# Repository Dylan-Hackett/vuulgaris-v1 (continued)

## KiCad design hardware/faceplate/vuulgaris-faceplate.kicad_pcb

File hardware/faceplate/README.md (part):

# Faceplate PCB

4-layer, **ENIG**. Carries the four capacitive scrub pads on L1 and the MSP430FR2675 on
the back. **The front is exposed gold on ground, and every printed mark is black soldermask**
([ADR 0013](../../docs/decisions/0013-gold-face-mask-ink.md)): order black mask, white silk,
ENIG, via covering "Plugged" (JLC's default; they do not offer tented on 4 layers, and POFV
would cap the pads' vias). 5 boards $79.80 on JLC's instant quote, 2026-09-29. Panel geometry comes from `../../mockups/generate-faceplate.py` — see the
handoff below for the size, which is not what older docs say.

## Status — 2026-09-29: placed, routed, gold face (ADR 0013); DRC clean

**Schematic done**, `mksch → netcheck` 145/145 over 41 nets, every block traced to a TI or
manufacturer figure in `design/design.py`. 54 parts: `U1` MSP430FR2675TPT; `C1`/`C2`
10µF + 100nF on DVCC, `C3` 1µF on VREG, `R1`/`C4` 47k + 1nF on RST (SLASEO5D Figures
10-1, 10-4); `R2`/`R3` 47k on P1.4/P1.5 (SLAU550 §3.3.2.1); `Y1` FC-135 + `C5`/`C6` 22pF
(Figure 10-2); the sixteen CapTIvate lines, **one pin from each block per pad**, each
through a TPD1E10B06 to GND on the electrode side and a 470R series resistor (`D11`–`D44`,
`R11`–`R44`, CapTIvate design guide); `E1`–`E4` the pads as symbols (RX0 on pins 1 and 5,
one net); `TP1`–`TP6` SBW and UART pads; `J1`.

**Pad copper is on the board** (2026-09-28): `E1`–`E4` are generated footprints, one via
per bar (763 vias, 37 bridges), from `design/mkpads.py`; ADR 0003, "Connecting the bars".
boardcheck parity is 0 over 145. **Placed and routed** — every piece of copper from a script,
rebuildable from zero ("Layout" below); DRC 0 errors, nothing unconnected; nothing on the top
layer but the pads, nothing under a pad but its own nets.

**`J1` is the hanxia HX JN2.54-2x5P TP H8.9, LCSC C41376028** (chosen 2026-09-28).
It has to be SMD: `J12`'s through-hole C5665 here would put ten pins through the **front
face**, in the 8mm gap between pads 3 and 4. It is Extended: JLC's Basic filter returns no
SMD 2x5 box header at all. Footprint `IDC-SMD_10P-P2.54_C41376028` is from hanxia's
drawing (`datasheets/hanxia-HX-JN2.54-2x5P-TP-H8.9.pdf`): pads 1.02 x 4.65 on 2.54mm,
11.50 overall; body 20.30 x 8.90, **9.60mm seated**, under the 10mm gap. The runner-up,
XFCN BH254VS-10P (C492446), is 10.5mm tall. The drawing marks pin 1 only by a triangle
on the key wall, so the footprint puts pin 1 on the key-side row at that end, as KiCad's
DIN 41651 footprint and `J12` both do. **Pin 1 and the key are settled from both
manufacturer drawings** (2026-09-28, §5).

## The loop

Same tools as the main board, with `--project faceplate` (`../kicad/tools/proj.py`).
From `hardware/kicad/`, with `set -o pipefail` whenever output is piped:

```bash
python3 tools/mksch.py --project faceplate && python3 tools/netcheck.py --project faceplate
python3 tools/boardcheck.py --project faceplate   # board pads vs netmap parity
python3 tools/drc.py --project faceplate          # KiCad's own DRC -- the clearance authority
python3 tools/drc.py --project faceplate --unrouted   # while placed but not routed: the ratsnest is not a failure
python3 tools/panelcheck.py --project faceplate   # outline, holes, OLED window, J1, the cable, pad copper, vias, walls
```

**Pad copper** is regenerated, never hand-edited: change `mockups/generate-faceplate.py`
(its `--check` must pass), then, under KiCad's Python,
`hardware/faceplate/design/mkpads.py` rewrites the four `SCRUB_PAD_216x10_Pn` footprints
and replaces `E1`–`E4` and every via on a `PADp_RXn` net. panelcheck fails if the board's
pads or vias differ from `copper()` by more than 1µm, or if the generator's via keepouts are
not exactly `J1`'s pad rows.

- **Intent** is `design/netmap.json`; **symbols, sheet positions, footprints** are
  `design/design.py`; values `design/values.json`. Never hand-edit the `.kicad_sch`.
  `J1`'s netmap was derived from the main board's `J12`, pin for pin — the ribbon is
  straight through — and `panelcheck` fails if the two ever disagree.
- **`panelcheck`** is this board's `place.py --check`. It derives everything from the
  generator, the placement file, and the main board itself (its `J12` and the Edge.Cuts
  cutout). Parts not placed or not yet sized are **TODO**, not failures; run it with
  `--strict` before plotting a fab package and every TODO fails.
- **Pin cache:** `design/kpins.json` is untracked. Rebuild it, from the repo root, with
  exactly this argument list (stock libraries first, the shared project library last):

  ```bash
  python3 hardware/kicad/tools/ksym.py --project faceplate /Applications/KiCad/KiCad.app/Contents/SharedSupport/symbols/*.kicad_sym hardware/kicad/lib/vuulgaris.kicad_sym
  ```
- **The board** was bootstrapped once by `design/mkboard.py` (KiCad's Python; it refuses
  to overwrite). From here it is edited like the main board's: scripted through pcbnew,
  or by hand in Pcbnew — and after a script writes, **File → Revert** before touching it.
- **Coordinates:** the faceplate board is drawn in panel coordinates, sheet = panel +
  (100, 50) (`panelgeo.FACE_ORG`). Panel y runs from the jack edge.
- The library is **shared** with the main board (`../kicad/lib/`, via this project's
  `sym-lib-table` / `fp-lib-table`). Footprints named `lib:name` in `design.py` come
  from elsewhere; a bare name means `vuulgaris.pretty`.
- DRC ran with one warning while `J1` was KiCad's stock footprint, which does not
  resolve in headless pcbnew. With the real part in the project library it is 0 and 0.
- Every check has been watched failing: a swapped netmap pin (netcheck, panelcheck), a
  track shorting pins 1 and 3 (DRC, boardcheck), `J1` moved 0.5mm or turned 180°, a pot
  hole 0.5mm undersize or 0.3mm off (panelcheck).

## Handoff from the main board — 2026-09-24

The main board is finished: DRC clean, fab package at `../vuulgaris-v1-fab.zip`. What
follows is fixed by it. The faceplate works around these, not the other way round.

### 1. Size: the generator is the source of truth — DONE 2026-09-27, 298.286 x 137.81mm

`generate-faceplate.py` gives **298.286 x 137.81mm**: the 130.81mm composition frame
(`composition_h_mm`, "board + 14" as of 2026-08-26) plus `panel_top_extra_mm` 2.0 and
`panel_bottom_extra_mm` 5.0, both pure extensions. `--check` re-derives with the extras
zeroed and fails if any placement row moves other than y += 2, and asserts the cavity is
1 + 118.81 + 6. Numbers still in circulation that are **superseded**: 130.81, "~285 x 155",
"298 x 154" (`panel-budget.md`). The mockup SVGs are now `mockups/faceplate-v1.svg` and
`faceplate-v1-FAB.svg`; they were `-298x139`, which was never their size.

- **+2mm at the top (jack) edge — DONE 2026-09-27.** Every one of the 24 rows in
  `../placement-panel-facing.txt` moved +2.000 in y and nothing else (compared in integer
  thousandths), `OY` went 7.000 → 9.000 in the same commit, and `place.py --check` reports
  all 24 on their holes with output identical to before; with the old `OY` it reports all
  24 off by 2.0. What the requirement was: The main board's top edge moved out 2mm on
  2026-09-23 so every edge connector ends flush with the wall (`design-state.md`, "Top
  edge extended 2mm"); the board is now 118.81mm. The knobs did not move, so **every
  panel y grows by exactly 2.000 and nothing may re-flow.** The generator centres and
  scales parts of the composition, so do not just raise `panel_h_mm`: add a pure offset,
  regenerate `../placement-panel-facing.txt`, and diff it against the old one — every
  row +2.000 in y, nothing else. In the **same commit** set `OY` in
  `../kicad/tools/place.py` from 7.000 to 9.000 (the comment above `ORG` explains), and
  `place.py --check` must still report all 24 panel parts on their holes. Get this wrong
  and `place.py` moves 24 parts on a routed board.
- **+5mm more at the bottom (back) edge — DECIDED 2026-09-27: yes, 137.81mm.** "Board +
  14" leaves 1mm behind the board, but the board slides in along y and needs 6mm of
  travel to clear the jacks (`design-state.md`, "Assembly": cavity 125.81 = 1 + 118.81 +
  6), so the box is 137.81 outside. A 132.81 panel on that box stops 5mm short of the
  back wall's outer face: its back screws (3mm in) would land over the cavity, and pad 4
  would end 0.36mm from the wall's inner face. The 5mm goes on below pad 4 and **moves no
  coordinates**. The cost is look: the pad block now sits 6.36mm below the divider and
  11.36mm above the bottom edge. Re-centring it would move ENC0 and SW4–SW9, which are
  centred on the pad block, so it stays.

Pads — **RECONCILED 2026-09-27: the generator's geometry, 10mm wide, 8mm gap, 18mm
pitch, 100 teeth.** See "Pad geometry" below and ADR 0003. Both candidates sat on the
same 18mm pitch, so the pad centres (and ENC0, centred on them) come out identical
either way; this was a sensing decision, not a placement one.

### 2. Stack-up: the pots are the datum, and the faceplate is structural

- Faceplate underside **10.0mm** above the main board (the pots' mounting surface),
  **1.6mm** thick, outer face at 11.6mm.
- **Do not go thicker.** The pots (Alpha RD902F) have 3.4mm of M7x0.75 thread above the
  outer face, for a 1.8mm nut plus washer.
- The six pot nuts are the **only** clamp. Encoders (EC12, 0.9mm of bushing through),
  toggles, buttons and the OLED locate but carry nothing. The whole main board hangs off
  the faceplate through those six nuts (`design-state.md`, "Panel mounting").
- **The 10mm gap is shared.** Anything on the faceplate's back (the MSP430, the ESD network,
  LEDs, the connector) sits in the same 10mm as the main board's top-side parts beneath it.
  The tall ones, board coordinates (panel = board + (6.995, 9.000) once §1's offset is in):

  | main-board part | height | board bbox x0,y0 – x1,y1 | faceplate room above |
  |---|---|---|---|
  | `C36`, `C37` electrolytics | 7.8mm | 190–200, 72.8–90.9 | ~2.2mm |
  | `C32`, `C33` electrolytics | 5.4mm | 190–201, 50.1–68.3 | ~4.6mm |
  | `U1` Daisy Patch SM | ~7mm soldered direct (no 3D model) | 243.8–283.9, 47.2–115.4 | ~3mm |
  | `VT301`/`302`/`401`/`402` vactrols | unknown (no 3D model) | 132.6–165.3, 58.0–67.8 and 134.9–167.5, 91.1–100.9 | read the Xvive drawing |

  Everything else on the main board's top is under 3.5mm apart from the panel parts, which
  pass through. Keep faceplate back-side parts low over those areas, or put them elsewhere.
  **The Daisy must be soldered in or on low-profile sockets** — standard 8.5mm sockets put
  it near 13mm and into the faceplate.

### 3. Holes

| part | hole | source |
|---|---|---|
| pots `RV1`–`RV6` | **7.5mm**, centred **0.17mm toward the top edge** of the panel coordinate | M7x0.75, washer ID 7.2 (Alpha drawing); true shaft is (0, −5.00) from the footprint origin, placed at −4.83 — `place.py` |
| buttons `SW4`–`SW9` | **7.2mm** | TS1103S drawing: plunger 6.2 ±0.2 at 14mm height; 0.4 a side at the largest, over the faceplate's ±0.25 float. Generator `mx_cut_d_mm` (the layout keeps `mx_hole_r_mm` = 3.3: changing that re-flows the column). Was 6.6 — 0.1 a side, a sticky button |
| toggles `SW1`/`SW2` | **5.6mm** | Dailywell drawing: 10-48 UNS bushing, 4.83 over the thread. Its 4.95 hole is for a switch hung from the panel by its nut; ours is soldered to the main board too, so the hole takes the bushing's ±0.25 and the faceplate's float. Generator `switch_hole_d_mm` |
| encoders `ENC1`–`ENC8` (EC12E) | **9.5mm** | ALPS EC12E2430803 drawing: body 5.5, then 7mm of M9x0.75 -- the static thread passes the faceplate; M9 + 0.5, the pots' margin |
| encoder `ENC0` (EC11L) | **10.0mm** | ALPS EC11L1525G01 drawing (LE2115L02G): **no thread** -- a 7mm bushing ends 9.5mm up, then a knurled 9.03mm shaft that turns and pushes 1.5mm passes the faceplate. Running clearance |
| OLED `DS1` | **window, 60.09 × 33.90mm**, r 1.0 corners, panel (208.50, 15.15)–(268.59, 49.05) | §4; the generator's `oled_window()` |

**Corners — filleted 2026-09-28, r 6mm** (generator `panel_corner_r_mm`), the wall
thickness. **The enclosure's outer corners take the same radius**; at 6 the cavity keeps
square inside corners, so the main board's outline is untouched. The cost: a panel screw
can no longer sit in the corner — at 3mm in, its head has to clear the arc, so corner
screws go **at least 9mm along the edge** (`panel_screw_corner_min_mm`, checked).

**Panel screws — 2026-09-28:** four M3, 3.4mm clearance holes, one at each corner: on the
long edges 9mm from the corner (x 9.00 / 289.29) and 3mm in (y 3.00 / 134.81), as close as
the r6 corner lets an M3 pan head sit. (Ten, along the edges, until the same day.) Generator
`panel_screws()`; the enclosure's threaded inserts go under them. The mockup draws the
heads; the board does not print them.
panelcheck checks all four corners.

The generator draws **no pot or encoder holes at all** — the r=8 and r=9.2 circles in the FAB
SVG are knob outlines, not cuts. The board's holes are drawn by `design/mkholes.py` from
`panelgeo.holes()`, and the OLED window from `panelgeo.oled_window()` (2026-09-28).
panelcheck `--strict` has no TODO left.

### 4. OLED

The module is **68 x 43mm on its own PCB, 4.2mm tall**, active area 55.01 x 27.49mm. It will
be raised **3–5mm** on a 1x9 socket plus four M3 standoffs in the corner holes already on
the main board. **Nylon standoffs, not metal:** the lower-left hole (297.55, 94.05) has a
`POS12V` trace on F.Cu 2.2mm from its centre, under the standoff's hex base, and a metal
one would put +12V a scratch of soldermask away from the module's mounting hole. The
other three holes have no copper within 3mm on either side. Its face then sits about **2.4–4.4mm** behind the
outer surface; at 5.8mm of lift it hits the faceplate. This answers Q18.

**The window — sized 2026-09-28** by the generator's `oled_window()`, from the HS242L01
drawing (datasheets/, section 1.4: PCB **72** × 43 — the spec table's "68 × 43" is the hole
pitch; AA 55.01 × 27.49 centred along the long axis, **5.11mm below the top edge and 10.4mm
above the bottom**; glass 62.1 × 39.85) and the stack-up. The lift is not chosen, so it is
sized at the **deepest**, 3mm: face 4.4mm below the outer surface.

| | |
|---|---|
| active area, panel | x 211.04–266.05, y 17.16–44.65 |
| window | x 208.50–268.59, y 15.15–49.05 (60.09 × 33.90), r 1.0 |
| AA in view, at 4.4mm deep | 45° from the player's side, 30° from the sides, 25° from the back |
| never nearer the glass edge than | 1.0mm, so past the pixels you see black glass, not the module PCB |

It is lopsided on purpose: the wide black band on the glass, where the flex bonds, is on
the player's side, which is the side that needs the margin. panelcheck checks the drawn
window against the generator, and the generator's module centre against the main board's
four `DS1` holes. **No chamfer:** JLC cannot bevel an internal cutout in FR4; the walls are
straight 1.6mm, and a hand bevel is optional.

### 5. The connector

Main board `J12`: 2x5 2.54mm box header (LCSC C5665), **on the BACK of the main board,
facing down** (moved 2026-09-25), ribbon to the faceplate.

**The route.** The main board has a **24 x 12mm cutout** directly beside `J12`, at board
(210, 97.5)–(234, 109.5) — sheet (310, 147.5)–(334, 159.5) — made for exactly this. The
faceplate's connector sits **over that cutout, facing down**; its ribbon plug hangs through
the hole in the main board, and the ribbon runs underneath to `J12`. That is what makes the
10mm faceplate gap workable: neither mated plug has to fit inside it. So:

- **Put the faceplate header over the cutout, centred on board (222.0, 103.5)** — panel
  (228.995, 112.5) once §1's offset is in. A 2x5 IDC plug is about 20.3 x 9mm; the hole is
  24 x 12, so 1.5–2mm clear per side. Checked 2026-09-26: `J12` is centred on the cutout
  in x (0.00mm), its body 1.44mm from the cutout's edge, nothing sits in the cutout, and
  nothing else is on the main board's back in the ribbon's path.
- **`J12`'s pin 1 is at its +x end (right, viewed from the top), on the row nearest the
  cutout.** Orient the faceplate header so the ribbon takes pin 1 to pin 1 — the two plugs
  sit at different depths, so it is easy to get backwards on paper. Done below.

  **Paper mock-up, 2026-09-28** (both boards read through pcbnew, panel coordinates):

  | | centre | pin 1 | odd row | key (slot) | faces |
  |---|---|---|---|---|---|
  | main `J12` (C5665) | (228.995, 100.5) | +x end | +y | +y wall (footprint silk) | down, from the main board's back |
  | faceplate `J1` (hanxia) | (228.995, 112.5) | +x end | +y | +y wall (hanxia drawing) | down, from the faceplate's back |

  The two headers are the **same orientation**, 12mm apart in y and at different heights;
  the cutout is on `J12`'s +y side, `U7` on its −y side (y 82). So the cable is a plain
  straight 10-way IDC ribbon, both sockets pressed on the **same face**, red stripe at the
  triangle on both. It leaves `J12`'s socket toward +y (the cutout, away from `U7`), sags
  under the main board, and rises into `J1`'s socket from its −y side: no fold, no twist.
  Pin mapping then does not depend on the sockets at all -- each is keyed into an
  identically oriented header, so wire n lands on pin n at both ends, whatever the socket's
  own convention.

  That argument needs both headers to carry the key on the same side of pin 1 -- were
  C5665's on the other wall, a keyed socket would sit 180° round at `J12` and the cable would
  map pin n to 11−n, `P3V3_MSP430` onto `GND`. **Closed from both manufacturer drawings,
  2026-09-28:** hanxia's (`datasheets/hanxia-HX-JN2.54-2x5P-TP-H8.9.pdf`) and BOOMELE's for
  C5665 (`datasheets/BOOMELE-C5665-2x5-box-header.pdf`, from JLC's part page -- LCSC's link
  is dead) both mould the pin-1 triangle on the **keyed wall**, at one end. So the key is on
  the pin-1 row on both parts, which is what both footprints assume (`J12`'s silkscreen,
  `J1`'s Fab notch). C5665's drawing also confirms `J12`'s 1.0mm holes on the 2.54 grid.
  What is left is assembly, not design: use a straight cable, both sockets on the same face,
  red stripe to the triangle. Plugging in the first real cable is still a free sanity check.
- **`U7` (the DKM10, ~10mm tall, on the back) is 1.03mm from `J12`'s far side.** A plug
  sits inside the header's shroud, so it fits; run the ribbon out toward the cutout, not
  toward `U7`.
- **Leave the ribbon slack.** The faceplate end is plugged in with the faceplate lifted and
  then lowered onto the pots, so the cable folds under the main board rather than spanning
  the 12mm between the plugs taut.
- **The case floor needs about 15mm below the main board** around `J12` and the cutout: a
  9.2mm header plus the mated plug and the ribbon's fold.

| pin | net | |
|---|---|---|
| 1 | `MSP_TEST` | |
| 3 | `MSP_RST` | driven by MCP23017 `U4` |
| 5 | `MSP430_RXD` | Daisy A3 (UART4 TX) → MSP430 |
| 7 | `MSP430_TXD` | MSP430 **drives** → Daisy A2 (UART4 RX) |
| 9 | `P3V3_MSP430` | its own AMS1117 (`U6`) on the main board |
| 2,4,6,8,10 | GND | |

The order runs backwards from the original (pin 1 was 3V3) because flipping the header to
the back mirrors it; every net kept its hole and its routing. **Pin 1 is the ribbon's red
stripe** — check it end to end with the faceplate header's orientation before ordering
that board.

**No I2C and no IRQ cross the cable** (`pin-allocation.md`, superseding design-state §9).
There is **no 5V** on it, by decision (ADR 0012).

### 6. MSP430

- UART on UCA0 at its **default** pins (P1.4 TXD / P1.5 RXD, pins 4/5), per
  `pin-allocation.md`. UART and I2C do not share pins (Q2, resolved).
- **Q21 CLOSED 2026-09-27.** SLAU550 §3.1 defers the BSL pins to the device datasheet;
  SLASEO5D Table 9-4 gives the UART BSL as **P1.4 transmit / P1.5 receive**, PT pins 4/5
  (Figure 7-1). The runtime UART and the BSL are the same two wires. The remapped
  P5.1/P5.2 (44/45) fallback is **dropped**: it only ever covered the BSL being elsewhere,
  and `J12` has no free position to carry it.
- **47k pull-ups on P1.4 and P1.5.** They are also TCK/TMS, and SLAU550 §3.3.2.1 warns that
  floating TCK/TMS raise the odds of landing in JTAG mode; the pull-ups also stop RXD
  floating while the Daisy boots. SLAU550's 1nF pull-downs are left off: they target the
  hardware entry sequence, which production never uses (blank-device detection, then
  software invocation).
- Q22: plan the crystal. SBW pads (TEST, RST, 3V3, GND) and test points on TX/RX/RST/TEST.

### 7. LEDs — DECIDED 2026-09-27: none. See ADR 0012.

No LEDs on this faceplate, and no 5V on `J12`. The main board orders as it is. What was on
the table (2026-09-23): one LED per zone, 16 in all, red/amber on 3.3V or white/RGB on a
new 5V pin, driven from the MSP430 through shift registers, lit beside the zones through
small windows and never PWM'd during a touch scan.

## Contents

```
vuulgaris-faceplate.kicad_pro / .kicad_sch / .kicad_pcb
sym-lib-table, fp-lib-table   point at ../kicad/lib, shared with the main board
design/netmap.json            the intent
design/design.py              symbols, sheet positions, footprints (read by mksch.py)
design/values.json            Value fields
design/mkboard.py             the one-shot board bootstrap
design/mkpads.py              pad footprints + E1-E4 + their vias, from the generator's copper()
design/mkplace.py             the one-shot placement of everything else (the table above)
design/mkholes.py             the whole Edge.Cuts layer: outline (r 6 corners), panel holes, screws, OLED window
design/mkbuses.py             the pad buses: every bar's via joined, each net out to the margin (deterministic)
design/mkcells.py             the network grid's cell vias, TVS/R stubs and TVS grounds (deterministic)
design/mkescape.py            J1 out along the pad 3-4 corridor to the test pads, R2, R3 and U1 (deterministic)
design/mkfanin.py             the L2 fan-in: every bus exit to its cell via, crossing-free (deterministic)
design/mkface.py              the front (ADR 0013): the GND gold on F.Cu, the art as black mask, the via patch and dots, the silk
design/mkzones.py             the L3 GND plane: solid, in the margin and the pad 3-4 corridor, never under a pad
design/mkroute.py             everything else, by Freerouting, fenced: no F.Cu, nothing under or between the pads
design/mklib_faceplate.py     the faceplate's own library parts (U1, Y1, the TVS, the pad symbol);
                              the pin table twice (Figure 7-1, Table 7-1), checked equal
DRC.rpt                       from tools/drc.py --project faceplate
fab/                          the fab outputs ("Fab package"); zipped to ../vuulgaris-faceplate-fab.zip
```

The SLAA891 cross-check came back as a connectivity finding, not a geometry one: TI's
elements are single bodies and ours are ratio-encoded islands, so there is no TI pattern to
diff against (ADR 0003, "Connecting the bars").

## Pad geometry

Authoritative spec is [ADR 0003](../../docs/decisions/0003-comb-pad-rx0-wraparound.md).
Summary: 4 channels, 5 segments, 4 zones, order `RX0 RX1 RX2 RX3 RX0`.

**Settled 2026-09-27**, and what `../../mockups/generate-faceplate.py` draws:

| | |
|---|---|
| Pad length | 216mm, independent of the gap (the "12 x pitch" lock was an artefact — Q17) |
| Pad width | **10mm** |
| Gap / pitch | **8mm / 18mm** |
| Teeth | **100** (25 per zone), 2.160mm pitch, 1.950mm wide, 0.21mm apart |
| Top-to-bottom gap | 0.20mm |
| Tooth fillet | 0.6mm, with the bar heights area-compensated so it does not bend the position curve |
| Min copper | 0.15mm enforced; the thinnest bar drawn is 0.197mm |

Why 10/8 rather than the old 12/6: the gap is the untested crosstalk variable (Q17) and
wants to be as wide as the pitch allows; bare copper already gives more signal than TI's
overlay designs, so 12mm buys sensitivity that is not needed at the cost of base
capacitance; and ratio encoding reads a finger that rides high or low across the pad as a
position error (top bars are RX0/RX2, bottom RX1/RX3), which a pad closer to a fingertip's
width keeps smaller. The old "80 teeth at 2.19mm" was the 175mm pad's number; at 216mm, 80
teeth would be 2.70mm.

The copper comes from `generate-faceplate.py`, not `comb-pad-generator.html`, whose
defaults are the superseded 175mm / 12mm pad. Its SVG is true mm scale with one `<g>` per
net.

**Cross-check against TI's own SLAA891 OpenSCAD output before committing copper.**

## Layout — placed and routed 2026-09-28

Settled with Dylan, in order: (a) one open via per bar (ADR 0003, "Connecting the bars");
(b) `U1` and its networks in the **right margin**, not the centre (ADR 0003, layout rules);
(c) the UART, 3V3, RST and TEST from `J1` along the **gap between pads 3 and 4**. Then:
route everything, **nothing on the top layer** (it is the scrub pads and nothing else).

All parts on B.Cu. The margin strip is panel x 277.14 (copper ends) to 292.29 (the wall's
inner face, where the faceplate rests on the wall top — panelcheck fails any back-side part
past it), over the Daisy (~3mm clear; nothing here is over 1.6mm).

| where (panel) | what |
|---|---|
| `U1` (284.45, 104.0) | CAP pins 23–39 face **up**, digital corner (46–5) down-right. Pins 1–5 run right to left along the bottom, 46–48 up the right side |
| the 4 × 4 grid over the CAP pins, rows y 77.15 / 83.15 / 89.15 / 95.15 (6mm apart) | the 16 networks. **Column = CapTIvate block** (RX0–RX3 at x 280.30 / 283.50 / 288.00 / 290.92, each over its own pins: CAP0 = 23–26 … CAP3 = 36–39), **row = pad** (1 at the top). Each cell: its via, the TVS on top of its 470R (pin 1 over pin 1, ground to the right; ADR 0004: the order and a short ground are what count) |
| middle channel, over pin 31 | `C3` 1µF VREG |
| across the corner by pins 1 / 48 | `C2` 100nF |
| right edge, y ~112–116 | `Y1` stood on end, `C5` (XIN) / `C6` (XOUT) beside its two pads |
| above the corridor's mouth, (278.3, 106.2) | `C1` 10µF 3V3 bulk — in the mouth it blocked RST, TXD and RXD in turn |
| under `U1`'s bottom-left | `C4` / `R1` (RST RC), `R3` (RXD pull-up, beside pin 5) |
| the corridor, x 240–262 | `TP1`–`TP6`, each ON its own line, staggered; `R2` (TXD pull-up) across the 3V3 and TXD lines; `TP4` (SBW GND) by `J1`'s GND via |

Pitches come from the silk (R0603's box is 1.47 × 2.93), not the library's small courtyards:
0 silk overlaps. The 31 silk-over-copper warnings are the library's R/C pin-1 dots, clipped
by the mask, as on the main board. The 470Rs' references stand on end beside them; the TVS
and test pad references are on B.Fab.

### How it is routed — rebuildable from zero

Every piece of copper comes from a script, in this order (KiCad's Python, from the repo root):

```bash
KPY=/Applications/KiCad/KiCad.app/Contents/Frameworks/Python.framework/Versions/3.9/bin/python3
$KPY hardware/faceplate/design/mkroute.py --unroute    # every track and via off
$KPY hardware/faceplate/design/mkplace.py --force      # the parts (the table above)
$KPY hardware/faceplate/design/mkholes.py              # Edge.Cuts: outline, holes, screws, OLED window
for s in mkpads mkbuses mkcells mkescape mkfanin mkzones; do $KPY hardware/faceplate/design/$s.py; done
$KPY hardware/faceplate/design/mkroute.py              # the rest, by Freerouting; re-run until DRC is clean
$KPY hardware/faceplate/design/mkface.py               # the front: gold, mask art, silk -- last, it clears the vias
```

**The corridor's right end is Dylan's hand reroute** (2026-09-29), now carried by the scripts.
The TXD and RXD hops and C4's GND via sit under the via patch. `mkescape.py` draws TXD, RXD,
RST and TEST end to end from its `TAIL` table, including the router's old runs past C4,
which the reroute kept, so the router finds those four nets complete. `mkfanin.py` jogs pad
4's RX0 exit to y 117.15.

| script | draws | how |
|---|---|---|
| `mkpads` | the pad copper, one via per bar | the generator's `copper()` |
| `mkbuses` | the buses: every bar's via joined, each net out to the margin | exact, L2 (RX0's join on L3); every via on a segment end |
| `mkcells` | each cell's via and B.Cu down to TVS pin 1 and R pin 1; each TVS's GND via; `C3`'s ground | exact; the vias staggered in height (below) |
| `mkescape` | `J1`'s escape, the corridor, its taps; RXD and TXD's hops to `U1`; `J1`'s GND | exact, B.Cu (hops on L2) |
| `mkfanin` | all 16 electrode lines, bus exit to cell via | exact, L2 |
| `mkzones` | the L3 GND plane: **solid**, margin + corridor, never under a pad | exact |
| `mkroute` | everything else: the B.Cu fan-out into `U1`, power, the last grounds, crystal | Freerouting, fenced (the gold is dropped from its DSN); then prunes dangling copper and stitches any GND pad with no path to the plane |
| `mkface` | the front: one GND zone on F.Cu less each pad's 2mm frame; F.Mask openings = the gold less the mask block (frames + via patch as one filleted outline), a dot over every other via outside the pads, and every art stroke; the right-hand numerals in silk on the patch | the generator's `face()`, `mask_block()`, `scale_marks()`, `panel_art()` (ADR 0013) |

**The electrode fan-in (`mkfanin`).** Each pad's lines leave its bus as RX0, RX2, RX1, RX3
(top to bottom) but the columns run RX0, RX1, RX2, RX3. Each cell's via sits at its own height
in the cell band, 0.5 apart, in the order the lines arrive, so each line runs level to its own
column and passes the others' vias at ≥ 0.5 — never another line. Pads 1–3 come in from the
strip left of the grid (column 0's via steps 0.4 right to open a fourth slot); pad 4's would
jam it, so they run under the corner group, up a strip at the right edge, and in from the
right, its via order reversed.

**The corridor (`mkescape`).** `J1`'s inner four signals climb into the 2.2mm channel between
its rows in pin order; past `J1` all five fan out to 1.3mm (RXD straight, the rest diverging
from it — fanned about a common point, the lines' corners came 0.197 apart) and run to the
margin. `J1`'s pins read TEST, RST, RXD, TXD, 3V3 but `U1`'s read DVCC, RST, TEST, TXD, RXD,
so RXD and TXD hop on L2 under the `C4`/`R1` group, TXD's under RXD's.

**The router's fences (`mkroute`).** F.Cu and In2.Cu are declared power layers, so it lays no
trace on either (a keepout over F.Cu also banned every via); no copper left of the margin
but the corridor, and there B.Cu only; everything already drawn locked; the buses handed over
only as a stub at each exit (it merges collinear locked segments and loses the vias between).
Its results vary run to run: re-run it (it is incremental -- what is routed stays) until DRC
shows nothing unconnected. With everything above scripted, the last rebuilds closed on the
first pass.

**Grounds.** Each TVS's ground pin gets a via beside it at its own height, where L2 is clear
of the fan-in lanes; in row 4 column 2 it goes up into the gap between rows 3 and 4, and
`C3` ties to column 1's. The router grounds the last few (row 4, columns 0 and 3; `C1`...),
and `mkroute` then stitches any GND pad still without a path to the plane: the nearest
spot where a via and a straight stub clear every other net (pcbnew's own shapes), never in
a pad. **The plane is solid**, not hatched: a via in a hatch hole touches nothing, and the
router takes the plane for solid; L2 is ~1.1mm above L3, so solid adds under 1pF to a
fan-in line.

**Netclass `CapTIvate`** (`/PAD*`, `/CAP*`): 0.15mm track, 0.15mm clearance (0.2 to anything
in GND or Default), vias 0.5 / 0.3 — TI wants sensor traces thin anyway. GND and Power 0.3mm,
all other vias 0.6 / 0.3: every net fits `U1`'s 0.5mm pitch.

panelcheck proves the fences held: nothing routed on F.Cu, and nothing — track, via or zone —
under a pad but that pad's own nets.

## Pin order is load-bearing

`RX0->E00, RX1->E01, RX2->E02, RX3->E03`. Generate the assignment in Design Center **first**,
then lay out to match. A swapped pair produces garbage interpolation on a board that passes
every electrical check.

## Per-electrode ESD network

4 CapTIvate lines x 4 pads = **16 of each** (settled 2026-09-28; was 20, see ADR 0004):
- RX0's two end groups join on the electrode side, first
- TPD1E10B06 TVS between that electrode net and ground
- 470R-1k series resistor from there to the CapTIvate pin

Place near the MCU with a low-impedance ground path.

Each pad takes **one pin from each CapTIvate block** (`RXn` of pad `p` to `CAPn.(p-1)`), not
one block; `../../docs/pin-allocation.md` has the table and TI's source.

## Fab package — 2026-09-29

`hardware/vuulgaris-faceplate-fab.zip`: gerbers, the JLC BOM and CPL, and a README with
the order options (black mask, white silk, ENIG, via covering **Plugged**, **Remove Mark**,
**bottom-side** assembly). After any board change, in the same commit, from `hardware/kicad/`:

```bash
CLI=/Applications/KiCad/KiCad.app/Contents/MacOS/kicad-cli; F=../faceplate
$CLI sch export python-bom --output $F/fab/vuulgaris-faceplate-bom.xml $F/vuulgaris-faceplate.kicad_sch && python3 tools/mkbom.py --project faceplate
python3 tools/mkcpl.py --project faceplate
$CLI pcb export gerbers --output $F/fab/ --no-protel-ext --layers "F.Cu,In1.Cu,In2.Cu,B.Cu,F.Paste,B.Paste,F.SilkS,B.SilkS,F.Mask,B.Mask,Edge.Cuts" $F/vuulgaris-faceplate.kicad_pcb
$CLI pcb export drill --output $F/fab/ --format excellon --excellon-separate-th --generate-map --map-format gerberx2 $F/vuulgaris-faceplate.kicad_pcb
(cd $F/fab && rm -f vuulgaris-faceplate-gerbers.zip && zip -q -X vuulgaris-faceplate-gerbers.zip vuulgaris-faceplate-*.gbr vuulgaris-faceplate-*.drl)   # must hold 15 files
python3 tools/mkfab.py --project faceplate
```

**The BOM**, 44 parts on 11 lines, every one JLC's. Stock read off JLC's parts library, not
LCSC's, on 2026-09-29:

| parts | LCSC | type | JLC stock |
|---|---|---|---|
| `U1` MSP430FR2675TPTR | C2052972 | Extended | **10** |
| `D11`–`D44` TI TPD1E10B06DPYR (X1-SON-2, 12pF) | C48260 | Extended | 287k |
| `J1` hanxia HX JN2.54-2x5P TP H8.9 | C41376028 | Extended | 4.2k |
| `C4` 1nF C0G | C163508 | Extended | 521k |
| `Y1` Epson FC-135 32.768kHz 12.5pF | C32346 | Basic | 470k |
| `R11`–`R44` 470R, `R1`–`R3` 47k | C23179, C25819 | Basic | millions |
| `C1` 10µF, `C2` 100nF, `C3` 1µF, `C5` `C6` 22pF C0G | C15850, C14663, C28323, C1653 | Basic | millions |

**U1 is the one to watch:** 10 in stock is every chip a 10-board run needs. The drop-in is
the MSP430FR2676 in the same PT package and pinout (SLASEO5), with 64KB/8KB:
TPTR C2053559 (1 in stock) or TPT C1338445 (pre-order, ~9 days).

**Rotations.** Every part is on the back, so `mkcpl.py` sends each as 180 − its angle. Each
of this board's own footprints was checked against JLC's EasyEDA footprint for its part,
and all share its frame: U1's (`LQFP-48_…-TL`) has pin 1 top-left like ours, not the −90
the usual LQFP rule gives; J1's has pin 1, the odd row and the key along its bottom, like
ours. A half turn on J1 would land 3.3V on GND through a keyed cable. TP1–TP6 and E1–E4 are
copper, in neither the BOM nor the CPL.

`tools/gerbercheck.py` stays main-board only. It fails any overlap of two flashed pads, and
here 763 vias sit on their own bars and 37 bridges overlap bars, by design; gerbers carry
no nets to tell those apart. panelcheck checks the same copper through pcbnew instead.

## Layout checklist

- [x] No ground under the electrodes: panelcheck, "nothing under a pad but its own nets"
      (zones included). In the margin the fan-in lines run over the solid L3 plane, ~1.1mm down.
      The gold face is ground **beside** the pads, 1.9mm off all round ("gold clear of every
      pad by its frame"), and over the fan-in lines only under the via patch, as a screen
      (ADR 0013; part of Q1)
- [x] RX0 end groups one net: the return runs on **L3** under its own pad's RX2 bars
      (mkbuses; on L2 it would enclose RX2) — same-pad, same-cycle ([Q24](../../docs/notes/open-questions.md))
- [x] MCU placement: right margin, not centred (ADR 0003, layout rules, 2026-09-28)
- [x] No electrode near an edge: pad copper x 61–277, y 62–126; walls are 6mm
- [x] Digital lines: along the gap between pads 3 and 4 to `J1`, which the main board fixes
      (ADR 0003); UART quiet during scans ([Q23](../../docs/notes/open-questions.md))
- [x] Minimum copper 0.15mm everywhere, no slivers at ramp ends (0.165mm, bridged)
- [x] CAPTIVATE-PGMR connection: `J1` itself, by jumpering the ribbon's `J12` end to the
      PGMR (ADR 0005, revised 2026-09-28). No separate connector.
- [x] 4 SBW test pads present (TEST, RST, 3V3, GND): `TP1`–`TP4`, beside `J1`
- [x] Test points on UART Tx/Rx, RST, TEST (there is no IRQ line — `pin-allocation.md`): `TP5`, `TP6`
- [x] Soldermask opening over all pad copper: every bar and bridge its own opening, exactly
      its copper (1:1; mask stands in the tooth gaps, 0.20 at the least; 2026-09-29), vias
      open both sides. panelcheck "pad mask openings == their copper"; KiCad DRC checks no
      opening spans two nets
- [x] Panel art (2026-09-29, ADR 0013): everything the mockup prints -- rules, dividers,
      semicircles, Attic numerals, the scale -- as black soldermask on the gold, and none of
      its part outlines (knobs, buttons, switches, OLED, screw heads). The right-hand numerals
      are silk, on the via patch. The frames and the patch are one block, filleted 2mm out,
      1mm in. panelcheck samples every stroke (ink where drawn, gold beside it) and the
      block's outline (mask 0.12 inside, gold 0.12 outside); every via outside the pads under
      the patch or a dot; silk == generator
- [x] Copper extended past the printed scale (endpoint trim eats a few mm at each end): the
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
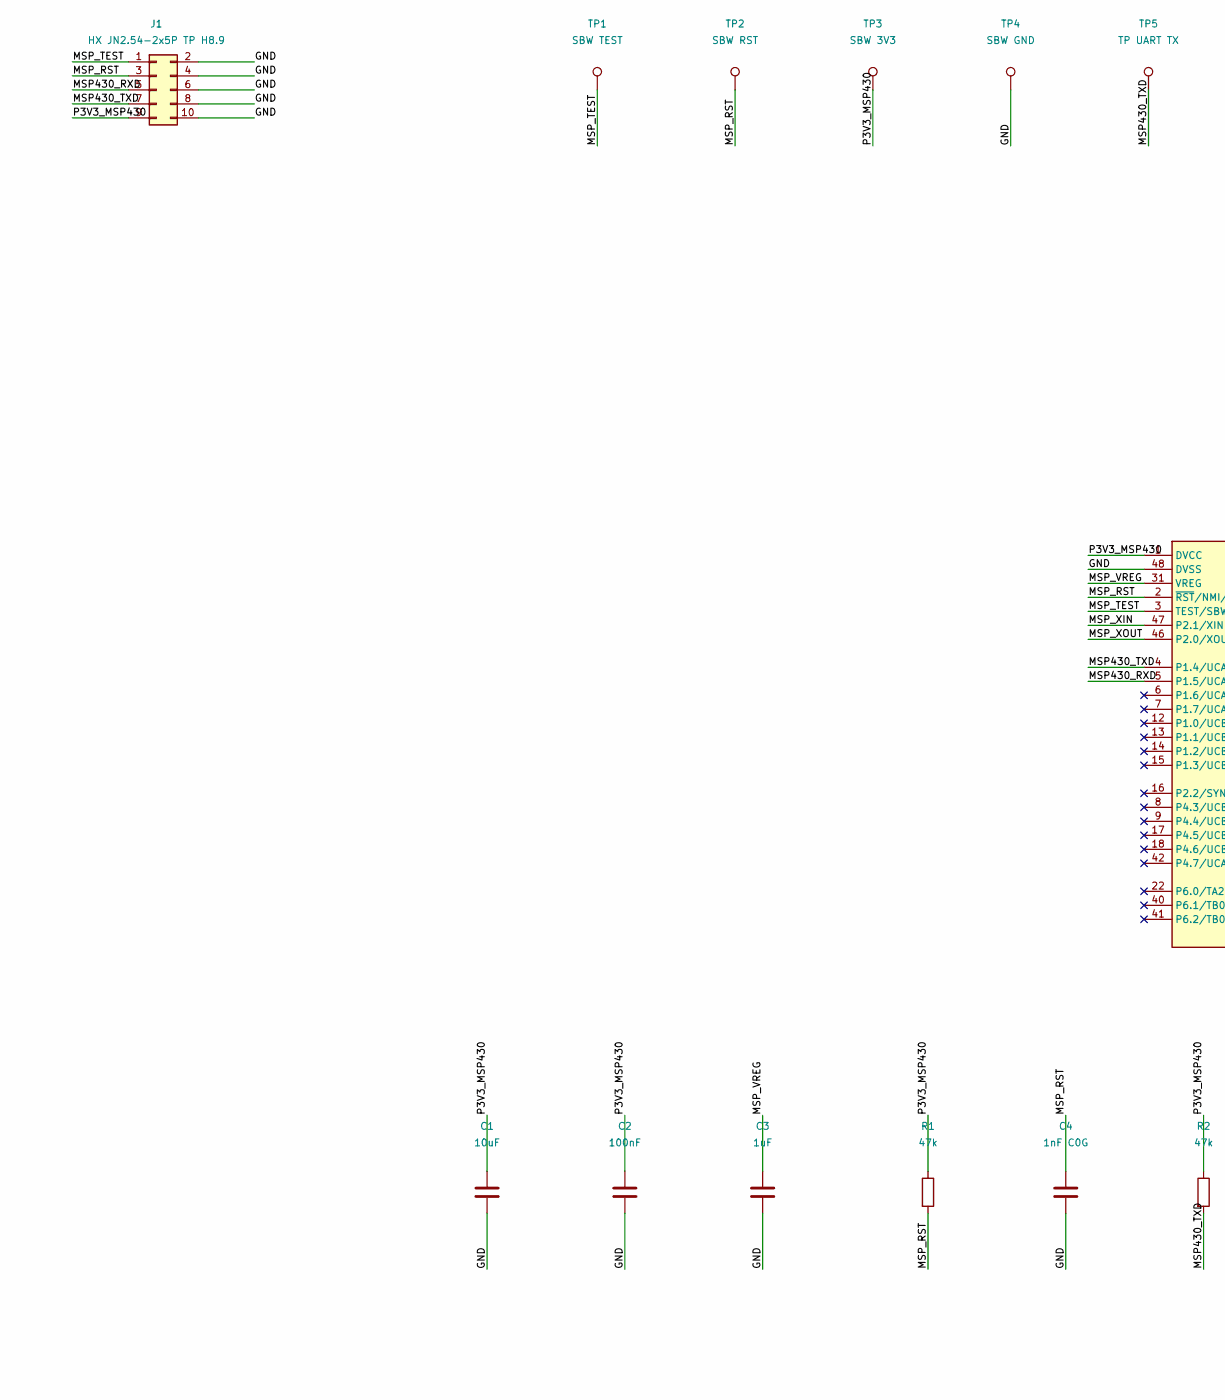
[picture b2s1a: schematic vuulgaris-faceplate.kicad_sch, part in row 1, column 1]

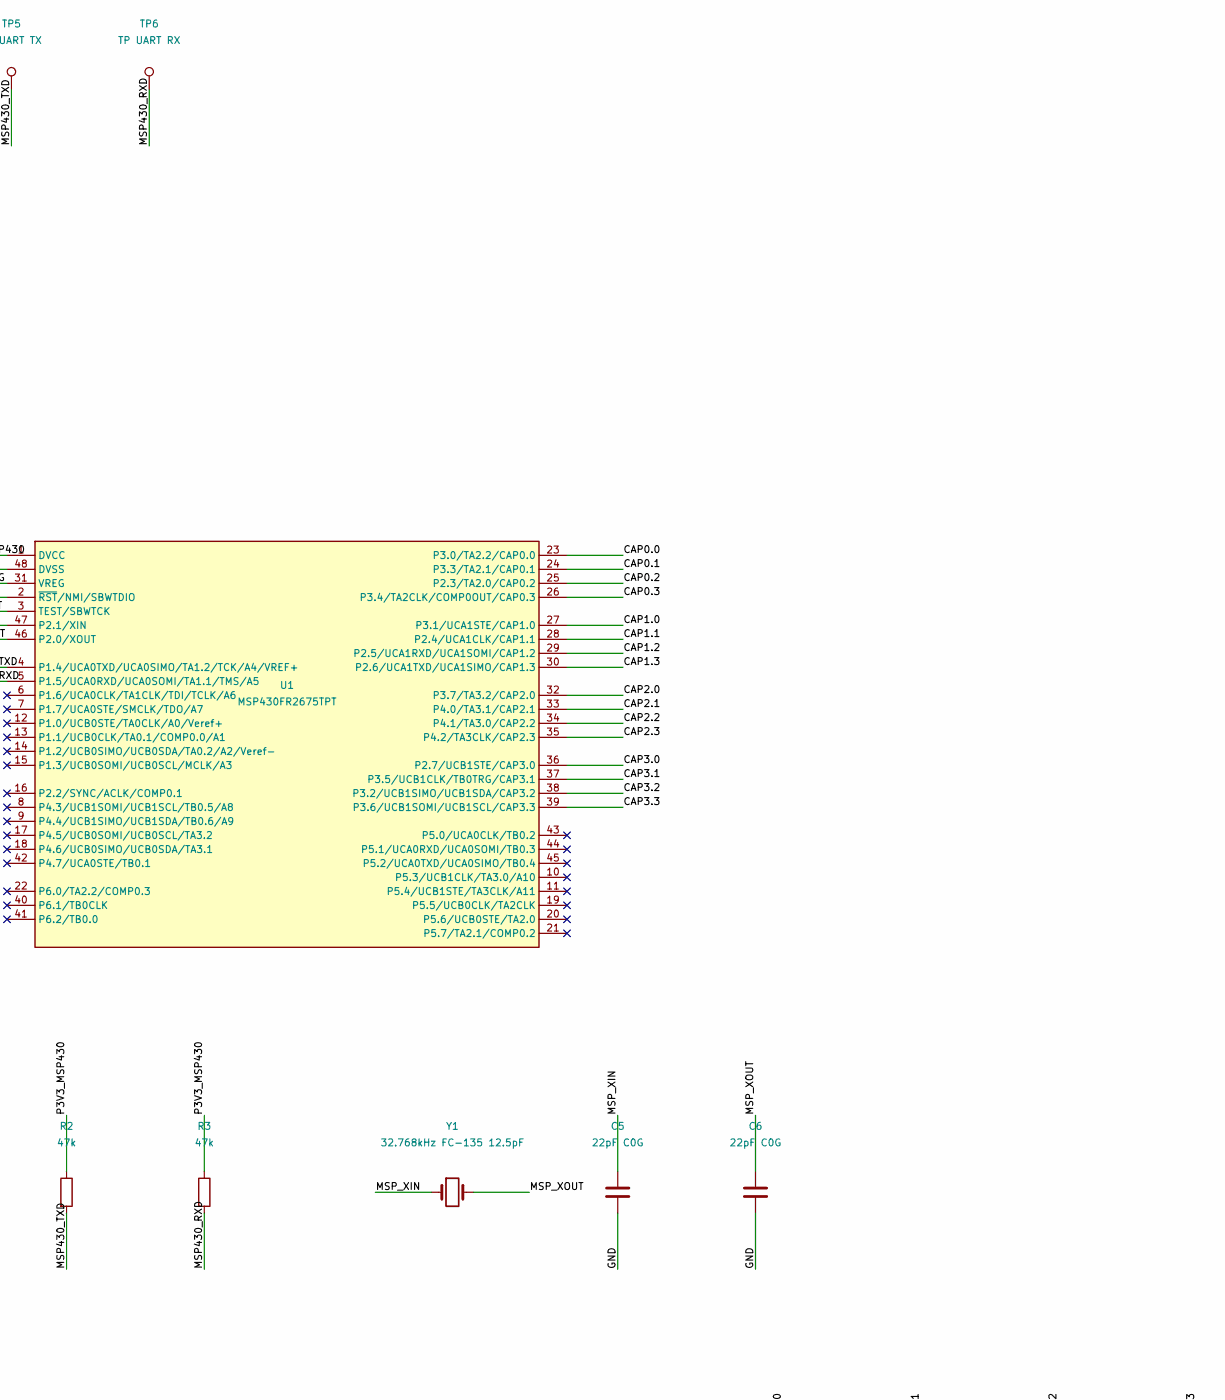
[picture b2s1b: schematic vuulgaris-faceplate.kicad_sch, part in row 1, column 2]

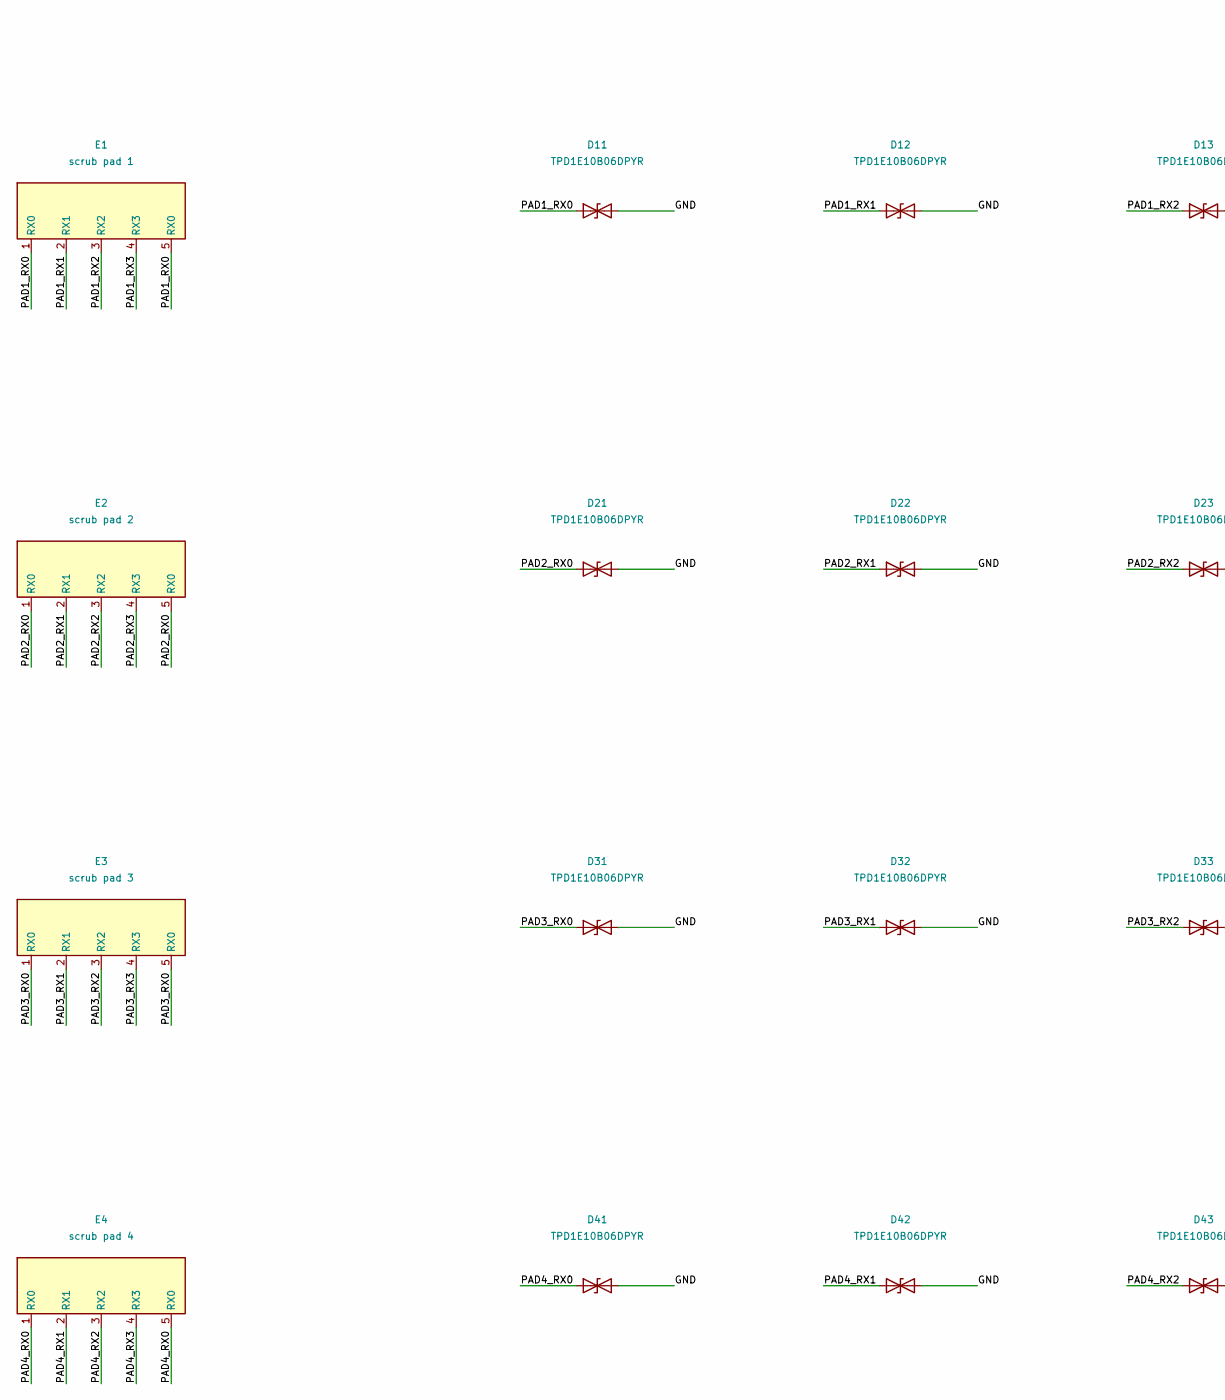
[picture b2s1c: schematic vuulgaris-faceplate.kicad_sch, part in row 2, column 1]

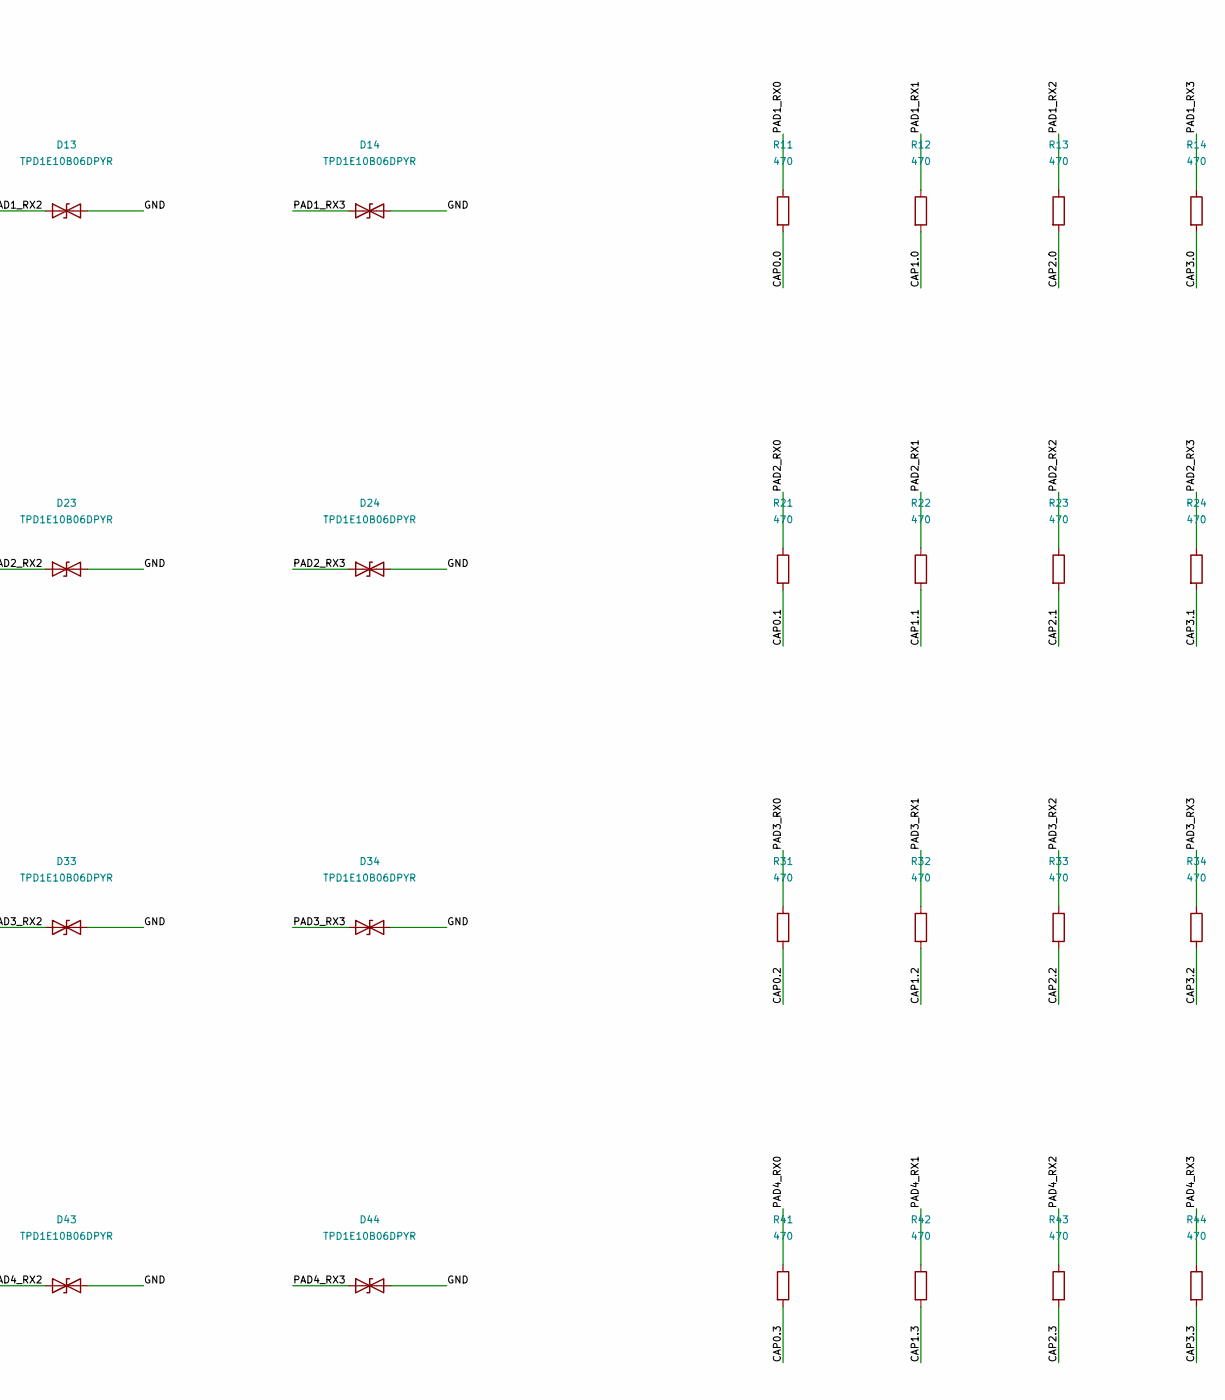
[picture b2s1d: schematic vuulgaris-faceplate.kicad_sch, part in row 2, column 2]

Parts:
C1: 10uF; C0805
C2: 100nF; C0603
C3: 1uF; C0805
C4: 1nF C0G; C0603
C5, C6: 22pF C0G; C0603
D11, D12, D13, D14, D21, D22, D23, D24, D31, D32, D33, D34, D41, D42, D43, D44: TPD1E10B06DPYR; X1SON-2_DPY0002A
E1: scrub pad 1; SCRUB_PAD_216x10_P1
E2: scrub pad 2; SCRUB_PAD_216x10_P2
E3: scrub pad 3; SCRUB_PAD_216x10_P3
E4: scrub pad 4; SCRUB_PAD_216x10_P4
J1: HX JN2.54-2x5P TP H8.9; IDC-SMD_10P-P2.54_C41376028
R1, R2, R3: 47k; R0603
R11, R12, R13, R14, R21, R22, R23, R24, R31, R32, R33, R34, R41, R42, R43, R44: 470; R0603
TP1: SBW TEST; TestPoint_Pad_D1.5mm
TP2: SBW RST; TestPoint_Pad_D1.5mm
TP3: SBW 3V3; TestPoint_Pad_D1.5mm
TP4: SBW GND; TestPoint_Pad_D1.5mm
TP5: TP UART TX; TestPoint_Pad_D1.5mm
TP6: TP UART RX; TestPoint_Pad_D1.5mm
U1: MSP430FR2675TPT; LQFP-48_7x7mm_P0.5mm_PT0048A
Y1: 32.768kHz FC-135 12.5pF; XTAL-SMD_FC-135_3.2x1.5mm

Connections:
/CAP0.0: R11.2, U1.23 (P3.0/TA2.2/CAP0.0)
/CAP0.1: R21.2, U1.24 (P3.3/TA2.1/CAP0.1)
/CAP0.2: R31.2, U1.25 (P2.3/TA2.0/CAP0.2)
/CAP0.3: R41.2, U1.26 (P3.4/TA2CLK/COMP0OUT/CAP0.3)
/CAP1.0: R12.2, U1.27 (P3.1/UCA1STE/CAP1.0)
/CAP1.1: R22.2, U1.28 (P2.4/UCA1CLK/CAP1.1)
/CAP1.2: R32.2, U1.29 (P2.5/UCA1RXD/UCA1SOMI/CAP1.2)
/CAP1.3: R42.2, U1.30 (P2.6/UCA1TXD/UCA1SIMO/CAP1.3)
/CAP2.0: R13.2, U1.32 (P3.7/TA3.2/CAP2.0)
/CAP2.1: R23.2, U1.33 (P4.0/TA3.1/CAP2.1)
/CAP2.2: R33.2, U1.34 (P4.1/TA3.0/CAP2.2)
/CAP2.3: R43.2, U1.35 (P4.2/TA3CLK/CAP2.3)
/CAP3.0: R14.2, U1.36 (P2.7/UCB1STE/CAP3.0)
/CAP3.1: R24.2, U1.37 (P3.5/UCB1CLK/TB0TRG/CAP3.1)
/CAP3.2: R34.2, U1.38 (P3.2/UCB1SIMO/UCB1SDA/CAP3.2)
/CAP3.3: R44.2, U1.39 (P3.6/UCB1SOMI/UCB1SCL/CAP3.3)
/GND: C1.2, C2.2, C3.2, C4.2, C5.2, C6.2, D11.2 (A2), D12.2 (A2), D13.2 (A2), D14.2 (A2), D21.2 (A2), D22.2 (A2), D23.2 (A2), D24.2 (A2), D31.2 (A2), D32.2 (A2), D33.2 (A2), D34.2 (A2), D41.2 (A2), D42.2 (A2), D43.2 (A2), D44.2 (A2), J1.2, J1.4, J1.6, J1.8, J1.10, TP4.1, U1.48 (DVSS)
/MSP430_RXD: J1.5, R3.2, TP6.1, U1.5 (P1.5/UCA0RXD/UCA0SOMI/TA1.1/TMS/A5)
/MSP430_TXD: J1.7, R2.2, TP5.1, U1.4 (P1.4/UCA0TXD/UCA0SIMO/TA1.2/TCK/A4/VREF+)
/MSP_RST: C4.1, J1.3, R1.2, TP2.1, U1.2 (~RST/NMI/SBWTDIO)
/MSP_TEST: J1.1, TP1.1, U1.3 (TEST/SBWTCK)
/MSP_VREG: C3.1, U1.31 (VREG)
/MSP_XIN: C5.1, U1.47 (P2.1/XIN), Y1.1
/MSP_XOUT: C6.1, U1.46 (P2.0/XOUT), Y1.2
/P3V3_MSP430: C1.1, C2.1, J1.9, R1.1, R2.1, R3.1, TP3.1, U1.1 (DVCC)
/PAD1_RX0: D11.1 (A1), E1.1 (RX0), E1.5 (RX0), R11.1
/PAD1_RX1: D12.1 (A1), E1.2 (RX1), R12.1
/PAD1_RX2: D13.1 (A1), E1.3 (RX2), R13.1
/PAD1_RX3: D14.1 (A1), E1.4 (RX3), R14.1
/PAD2_RX0: D21.1 (A1), E2.1 (RX0), E2.5 (RX0), R21.1
/PAD2_RX1: D22.1 (A1), E2.2 (RX1), R22.1
/PAD2_RX2: D23.1 (A1), E2.3 (RX2), R23.1
/PAD2_RX3: D24.1 (A1), E2.4 (RX3), R24.1
/PAD3_RX0: D31.1 (A1), E3.1 (RX0), E3.5 (RX0), R31.1
/PAD3_RX1: D32.1 (A1), E3.2 (RX1), R32.1
/PAD3_RX2: D33.1 (A1), E3.3 (RX2), R33.1
/PAD3_RX3: D34.1 (A1), E3.4 (RX3), R34.1
/PAD4_RX0: D41.1 (A1), E4.1 (RX0), E4.5 (RX0), R41.1
/PAD4_RX1: D42.1 (A1), E4.2 (RX1), R42.1
/PAD4_RX2: D43.1 (A1), E4.3 (RX2), R43.1
/PAD4_RX3: D44.1 (A1), E4.4 (RX3), R44.1

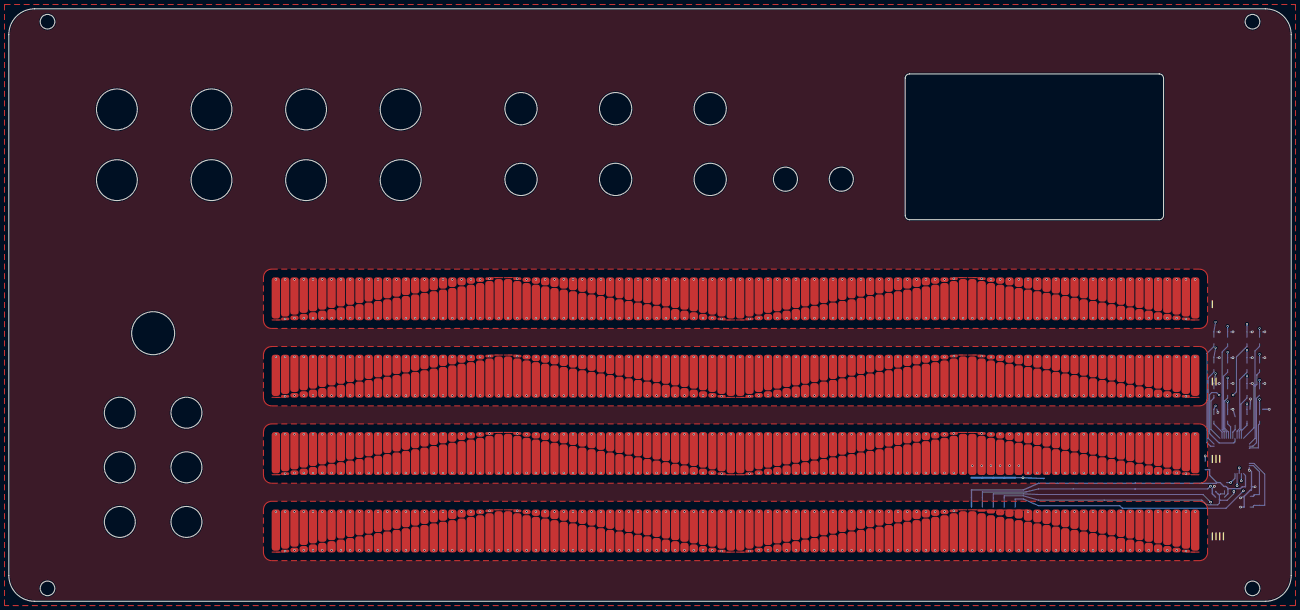
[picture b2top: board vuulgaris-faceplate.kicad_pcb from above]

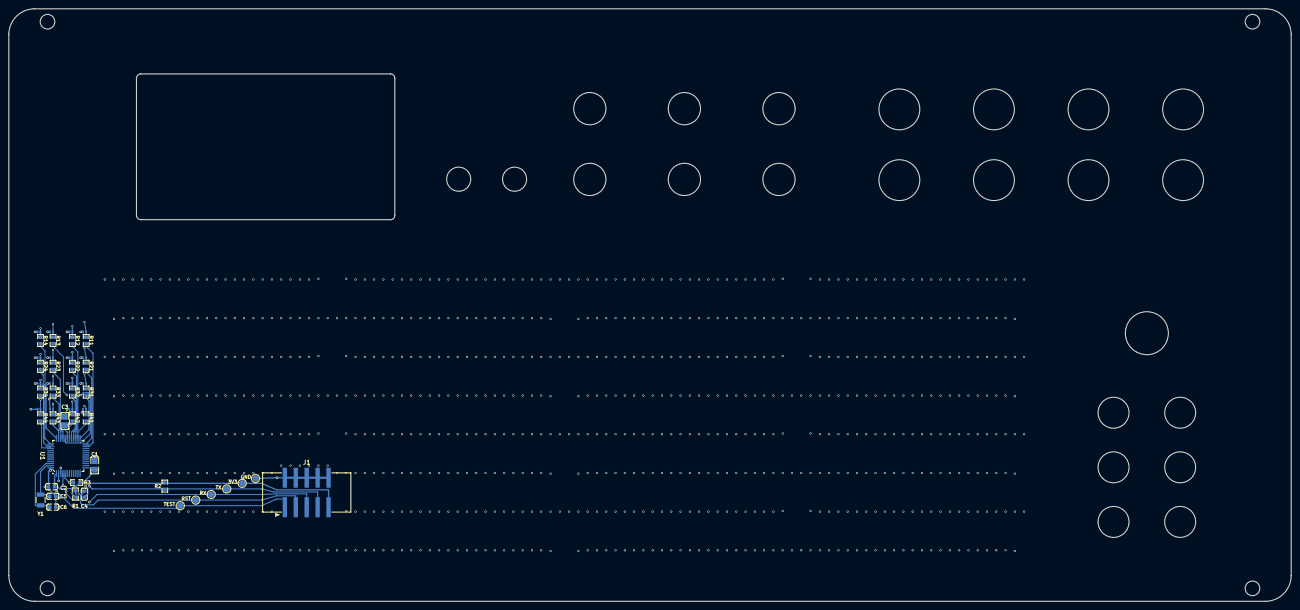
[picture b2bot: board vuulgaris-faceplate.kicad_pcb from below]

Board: 4 copper layers, 298.3 x 137.8 mm, 54 parts (50 on the bottom side), 41 nets.

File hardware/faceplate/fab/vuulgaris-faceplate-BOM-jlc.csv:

Comment,Designator,Footprint,LCSC Part #
100nF,C2,C0603,C14663
10uF,C1,C0805,C15850
1nF C0G,C4,C0603,C163508
1uF,C3,C0805,C28323
22pF C0G,"C5,C6",C0603,C1653
32.768kHz FC-135 12.5pF,Y1,XTAL-SMD_FC-135_3.2x1.5mm,C32346
470,"R11,R12,R13,R14,R21,R22,R23,R24,R31,R32,R33,R34,R41,R42,R43,R44",R0603,C23179
47k,"R1,R2,R3",R0603,C25819
HX JN2.54-2x5P TP H8.9,J1,IDC-SMD_10P-P2.54_C41376028,C41376028
MSP430FR2675TPT,U1,LQFP-48_7x7mm_P0.5mm_PT0048A,C2052972
TPD1E10B06DPYR,"D11,D12,D13,D14,D21,D22,D23,D24,D31,D32,D33,D34,D41,D42,D43,D44",X1SON-2_DPY0002A,C48260
